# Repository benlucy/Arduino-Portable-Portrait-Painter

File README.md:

# Arduino-Portable-Portrait-Painter
Code to run Arduino based portable portrait painter

Mechanical Build on Instructables.com (coming soon)

Working machine: https://www.youtube.com/watch?v=U5dt6qbI_Uw 

-------------------------------------------------------------------------------  
  
Compiling in Arduino IDE:  
  
1. Download all files
2. Copy "src/lib/LiveOV7670Library" and "src/lib/Adafruit_GFX_Library" to Arduino "libraries" folder (If you already have "Adafruit_GFX_Library" then you don't have to copy that)
3. Open "src/LiveOV7670/LiveOV7670.ino" in Arduino IDE
4. Select Tools->Board->Arduino/Genuino Mega or Mega 2560
5. Select Tools->Processor->ATmega2560 (Mega 2560)
  
-------------------------------------------------------------------------------

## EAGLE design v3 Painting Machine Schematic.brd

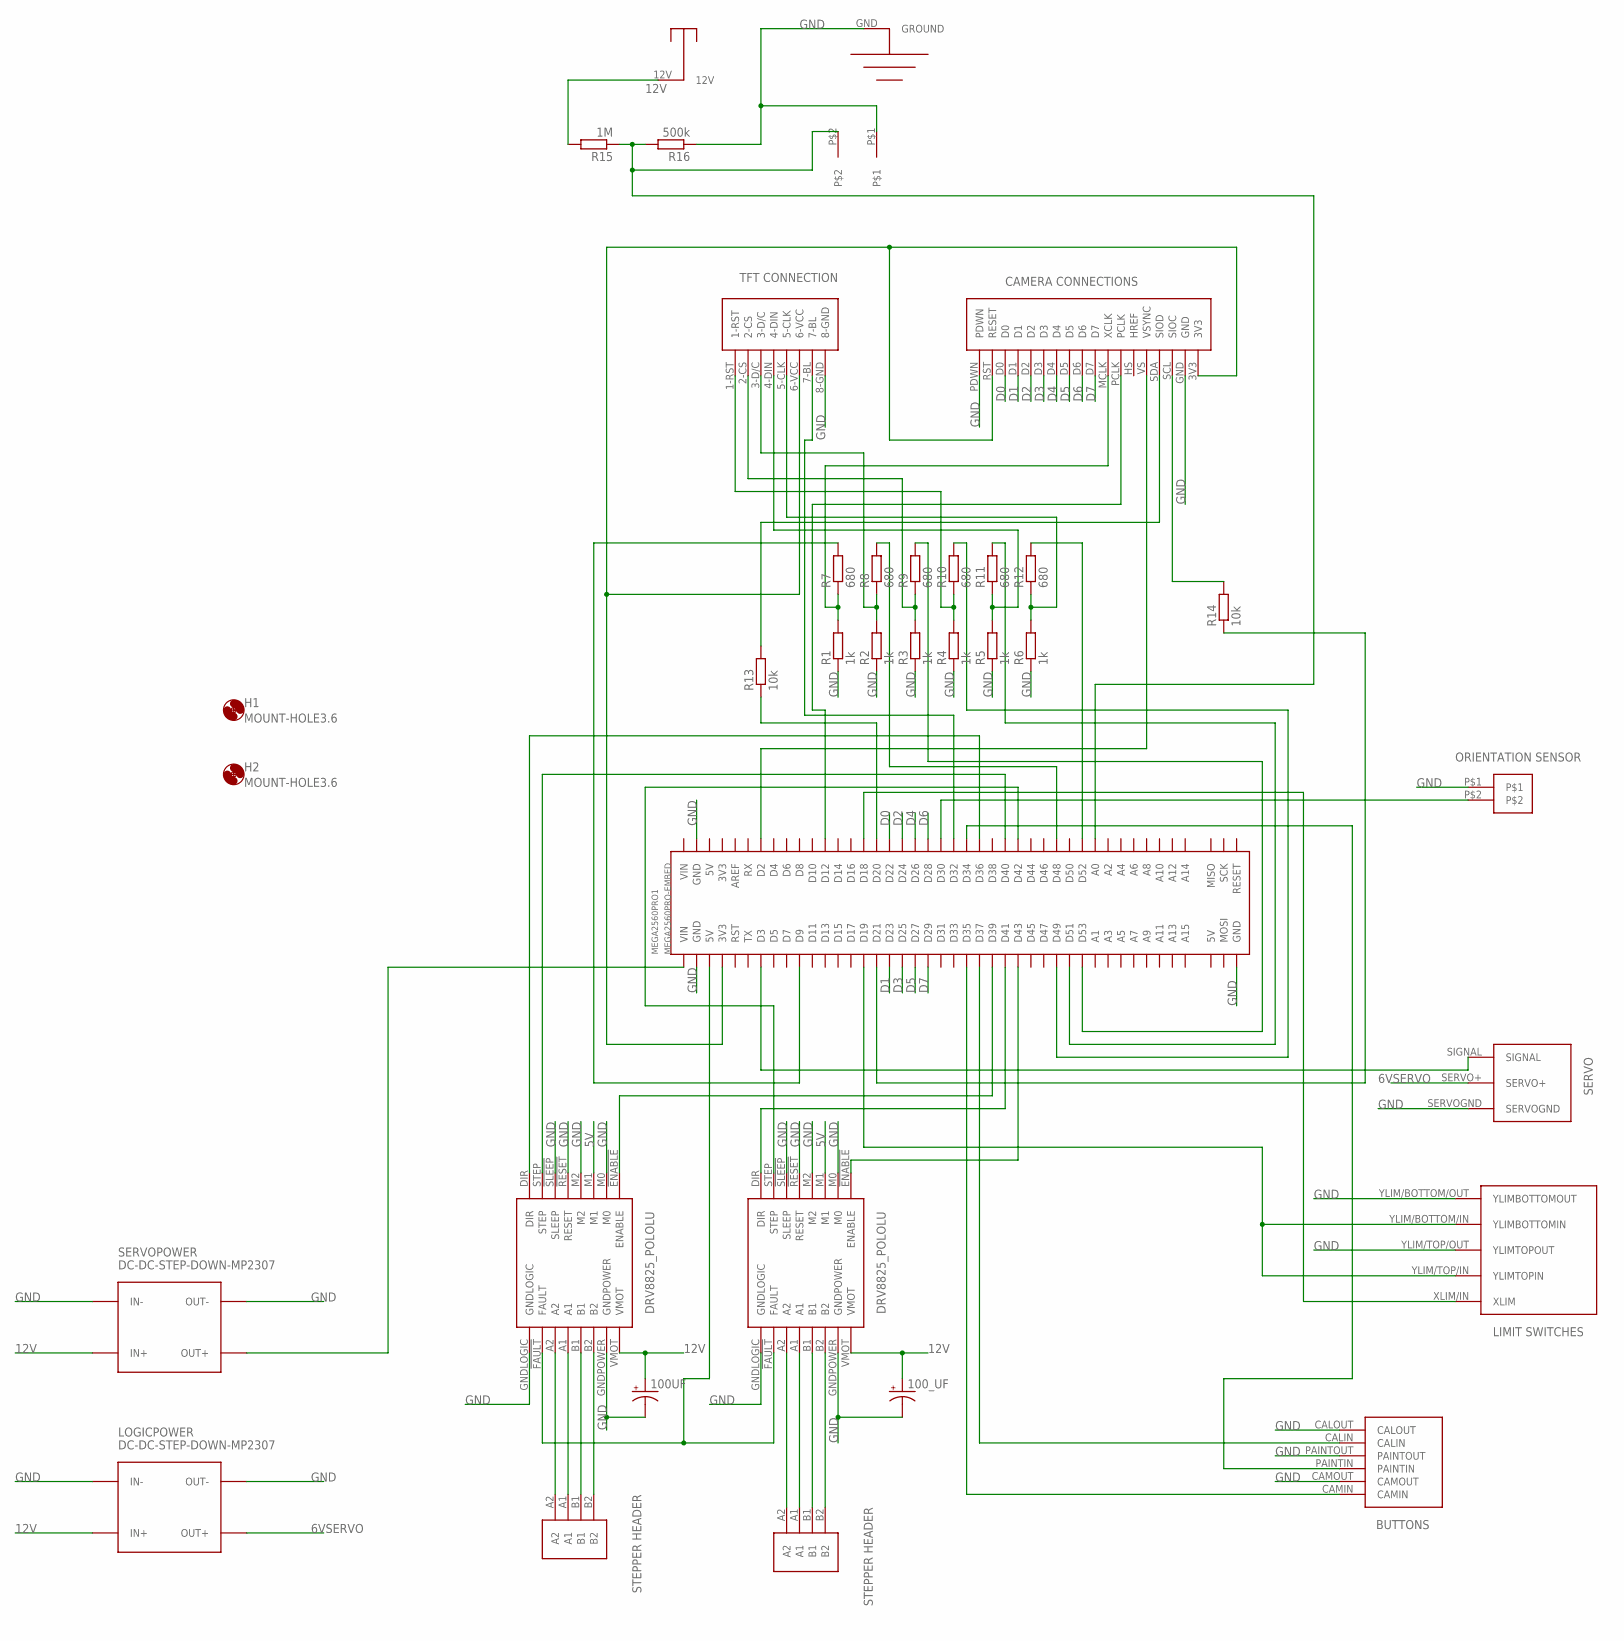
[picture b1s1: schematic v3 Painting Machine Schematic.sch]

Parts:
100UF, 100_UF: CPOL-USB45181B; B45181B
H1, H2: MOUNT-HOLE3.6; 3,6
LOGICPOWER: DC-DC-STEP-DOWN-MP2307
MEGA2560PRO1: MEGA2560PRO-EMBED
R1, R2, R3, R4, R5, R6: 1k; 0207/7
R7, R8, R9, R10, R11, R12: 680; 0207/7
R13, R14: 10k; 0207/7
R15: 1M; 0207/7
R16: 500k; 0207/7
SERVOPOWER: DC-DC-STEP-DOWN-MP2307
U$1, U$2: DRV8825_POLOLU_CARRIER; DRV8825_POLOLU
U$4: TFT/CONNECTIONS; TFTCONNECTIONS
U$5: OV7670CONNECTIONS; CAMERACONNECTIONS
U$6: ORIENTATIONSENSOR
U$7: 12V; VCC
U$8: GROUND
U$9, U$10: STEPPER_HEADER
U$11: SERVO
U$12: LIMITSWITCHES
U$13: BUTTONS; INPUTBUTTONS
U$14: CERAMICCAPACITOR

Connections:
5V: U$1.M1, U$2.M1
6VSERVO: LOGICPOWER.OUT+, U$11.SERVO+
12V: 100UF.+, 100_UF.+, LOGICPOWER.IN+, R15.2, SERVOPOWER.IN+, U$1.VMOT, U$2.VMOT, U$7.12V
D0: MEGA2560PRO1.D22, U$5.D0
D1: MEGA2560PRO1.D23, U$5.D1
D2: MEGA2560PRO1.D24, U$5.D2
D3: MEGA2560PRO1.D25, U$5.D3
D4: MEGA2560PRO1.D26, U$5.D4
D5: MEGA2560PRO1.D27, U$5.D5
D6: MEGA2560PRO1.D28, U$5.D6
D7: MEGA2560PRO1.D29, U$5.D7
GND: 100UF.-, 100_UF.-, LOGICPOWER.IN-, LOGICPOWER.OUT-, MEGA2560PRO1.GND@1 (GND), MEGA2560PRO1.GND@2 (GND), MEGA2560PRO1.GND@3 (GND), R1.1, R2.1, R3.1, R4.1, R5.1, R6.1, R16.1, SERVOPOWER.IN-, SERVOPOWER.OUT-, U$1.!RESET (RESET), U$1.!SLEEP (SLEEP), U$1.GNDLOGIC, U$1.GNDPOWER, U$1.M0, U$1.M2, U$2.!RESET (RESET), U$2.!SLEEP (SLEEP), U$2.GNDLOGIC, U$2.GNDPOWER, U$2.M0, U$2.M2, U$4.8-GND, U$5.GND, U$5.PDWN, U$6.P$1, U$8.GND, U$11.SERVOGND, U$12.YLIM/BOTTOM/OUT (YLIMBOTTOMOUT), U$12.YLIM/TOP/OUT (YLIMTOPOUT), U$13.CALOUT, U$13.CAMOUT, U$13.PAINTOUT, U$14.P$1
unnamed: U$2.A2, U$9.A2
unnamed: U$2.A1, U$9.A1
unnamed: U$2.B1, U$9.B1
unnamed: U$2.B2, U$9.B2
unnamed: U$1.A2, U$10.A2
unnamed: U$1.A1, U$10.A1
unnamed: U$1.B1, U$10.B1
unnamed: U$1.B2, U$10.B2
unnamed: MEGA2560PRO1.D9, R7.2
unnamed: MEGA2560PRO1.D48, R8.2
unnamed: MEGA2560PRO1.D53, R9.2
unnamed: MEGA2560PRO1.D49, R10.2
unnamed: R5.2, R11.1, U$4.4-DIN
unnamed: R6.2, R12.1, U$4.5-CLK
unnamed: MEGA2560PRO1.D12, U$5.PCLK
unnamed: MEGA2560PRO1.D52, R12.2
unnamed: MEGA2560PRO1.D51, R11.2
unnamed: R4.2, R10.1, U$4.1-RST
unnamed: R3.2, R9.1, U$4.2-CS
unnamed: R2.2, R8.1, U$4.3-D/C
unnamed: MEGA2560PRO1.D20, R13.1
unnamed: R1.2, R7.1, U$5.MCLK (XCLK)
unnamed: R13.2, U$5.SDA (SIOD)
unnamed: MEGA2560PRO1.D21, R14.1
unnamed: R14.2, U$5.SCL (SIOC)
unnamed: MEGA2560PRO1.3V3@1 (3V3), U$4.6-VCC, U$5.3V3, U$5.RST (RESET)
unnamed: MEGA2560PRO1.D2, U$5.VS (VSYNC)
unnamed: MEGA2560PRO1.D3, U$11.SIGNAL
unnamed: MEGA2560PRO1.D30, U$6.P$2
unnamed: MEGA2560PRO1.D19, U$12.YLIM/BOTTOM/IN (YLIMBOTTOMIN), U$12.YLIM/TOP/IN (YLIMTOPIN)
unnamed: MEGA2560PRO1.D18, U$12.XLIM/IN (XLIM)
unnamed: MEGA2560PRO1.D35, U$13.CAMIN
unnamed: MEGA2560PRO1.D37, U$13.CALIN
unnamed: MEGA2560PRO1.D34, U$13.PAINTIN
unnamed: MEGA2560PRO1.D41, U$1.DIR
unnamed: MEGA2560PRO1.D43, U$1.!ENABLE (ENABLE)
unnamed: MEGA2560PRO1.D39, U$2.!ENABLE (ENABLE)
unnamed: MEGA2560PRO1.D42, U$1.STEP
unnamed: MEGA2560PRO1.D40, U$2.STEP
unnamed: MEGA2560PRO1.D36, U$2.DIR
unnamed: MEGA2560PRO1.5V@1 (5V), U$1.!FAULT (FAULT), U$2.!FAULT (FAULT)
unnamed: MEGA2560PRO1.D32, U$4.7-BL
unnamed: MEGA2560PRO1.A0, R15.1, R16.2, U$14.P$2
VIN: MEGA2560PRO1.VIN@1 (VIN), SERVOPOWER.OUT+

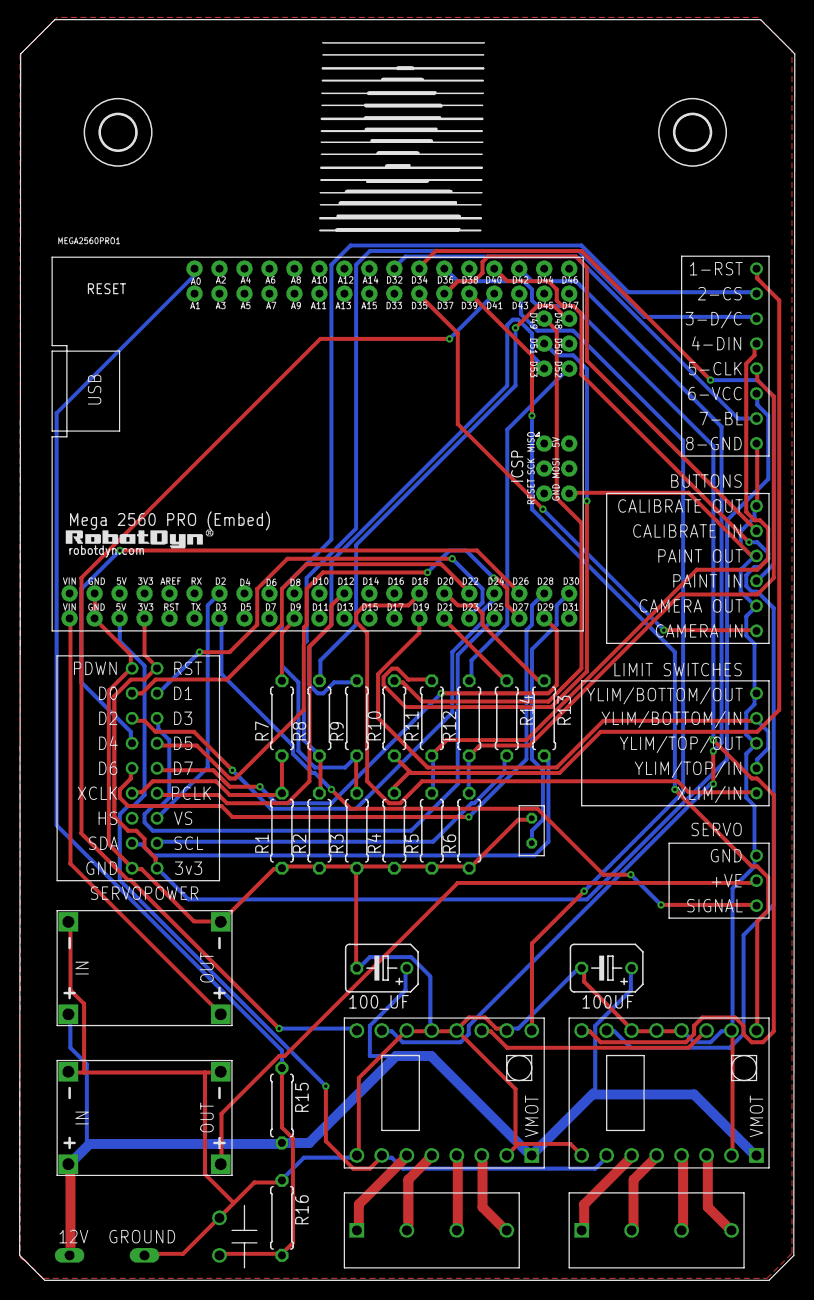
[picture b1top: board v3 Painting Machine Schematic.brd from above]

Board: 2 copper layers, 78.8 x 128.2 mm, 36 parts (0 on the bottom side), 56 nets.

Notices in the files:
parts and their libraries:
diy-modules: Released under the Creative Commons Attribution 4.0 International License: http://creativecommons.org/licenses/by/4.0
